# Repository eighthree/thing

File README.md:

# thing
Charlieplex matrix LED display with accelerometer

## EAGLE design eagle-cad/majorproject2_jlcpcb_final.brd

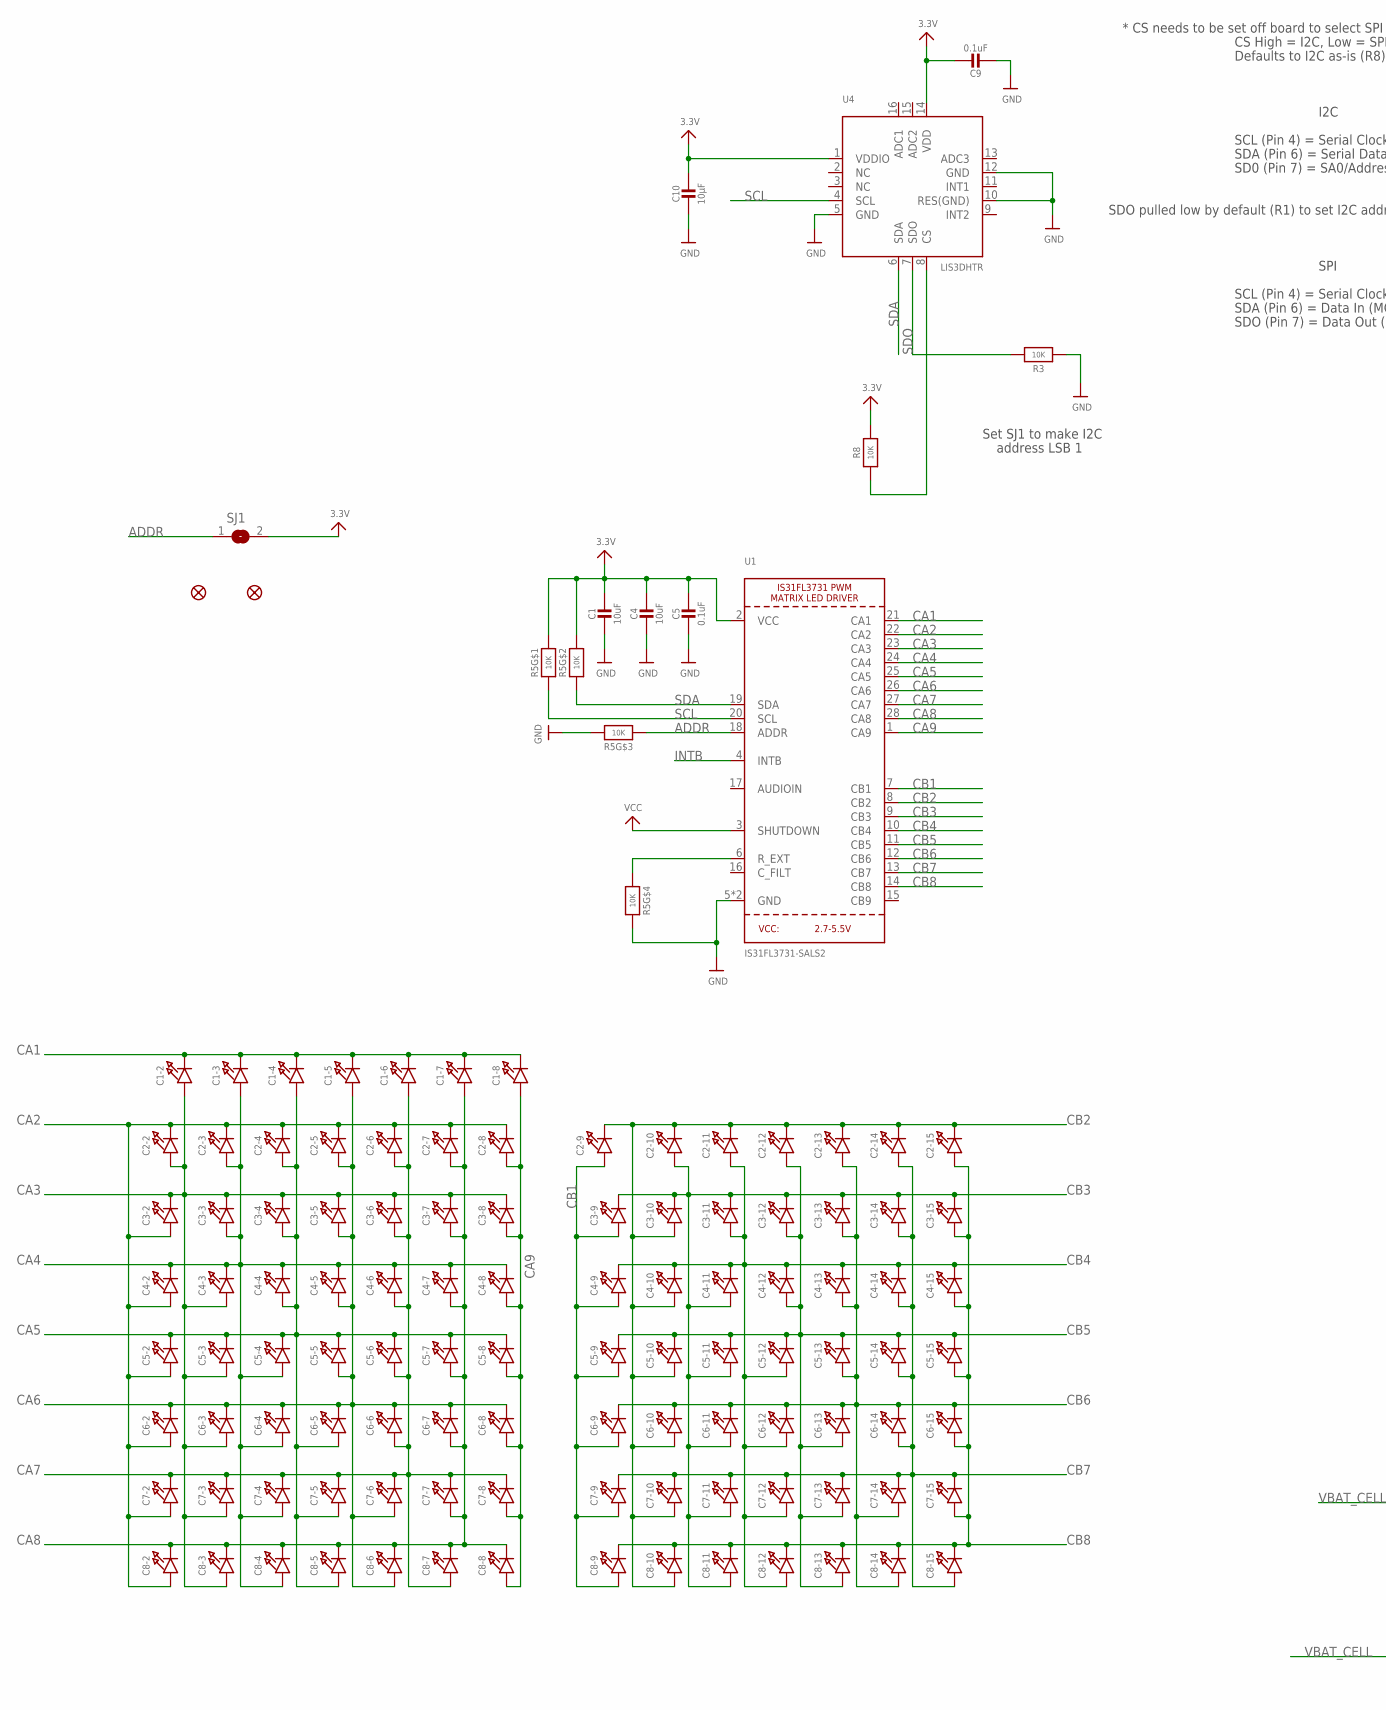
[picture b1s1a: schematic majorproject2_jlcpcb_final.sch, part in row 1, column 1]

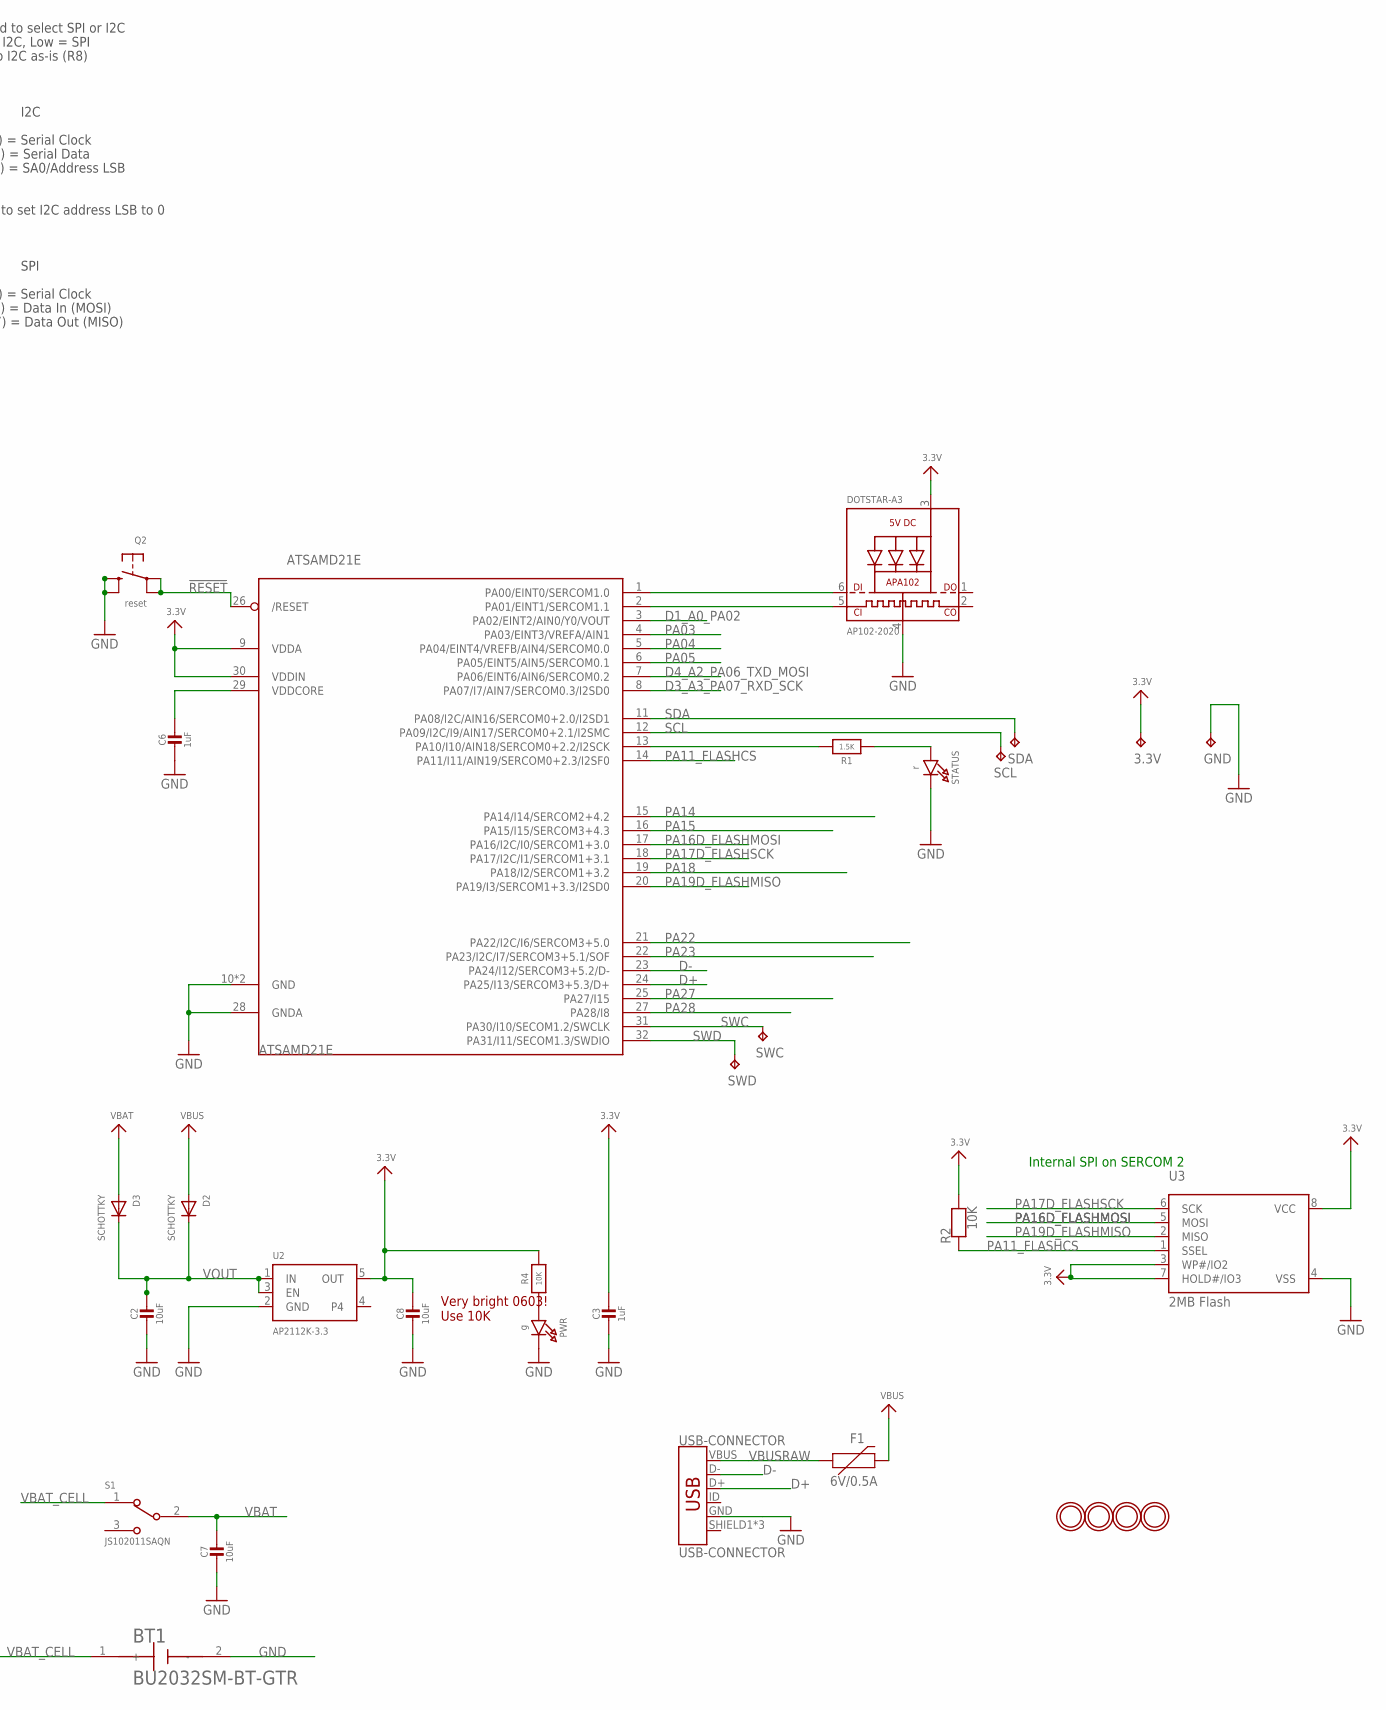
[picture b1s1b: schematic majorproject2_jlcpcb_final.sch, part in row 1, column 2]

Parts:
3.3V: TPB1,27; B1,27
ATSAMD21E: ATSAMD21E; QFN32_5MM
BT1: BU2032SM-BT-GTR; BAT_BU2032SM-BT-GTR
C1, C2, C4, C7, C8: 10uF; 0805-NO
C1-2, C1-3, C1-4, C1-5, C1-6, C1-7, C1-8, C2-2, C2-3, C2-4, C2-5, C2-6, C2-7, C2-8, C2-9, C2-10, C2-11, C2-12, C2-13, C2-14, C2-15, C3-2, C3-3, C3-4, C3-5, C3-6, C3-7, C3-8, C3-9, C3-10, C3-11, C3-12, C3-13, C3-14, C3-15, C4-2, C4-3, C4-4, C4-5, C4-6, C4-7, C4-8, C4-9, C4-10, C4-11, C4-12, C4-13, C4-14, C4-15, C5-2, C5-3, C5-4, C5-5, C5-6, C5-7, C5-8, C5-9, C5-10, C5-11, C5-12, C5-13, C5-14, C5-15, C6-2, C6-3, C6-4, C6-5, C6-6, C6-7, C6-8, C6-9, C6-10, C6-11, C6-12, C6-13, C6-14, C6-15, C7-2, C7-3, C7-4, C7-5, C7-6, C7-7, C7-8, C7-9, C7-10, C7-11, C7-12, C7-13, C7-14, C7-15, C8-2, C8-3, C8-4, C8-5, C8-6, C8-7, C8-8, C8-9, C8-10, C8-11, C8-12, C8-13, C8-14, C8-15: LED0603_NOOUTLINE; CHIPLED_0603_NOOUTLINE
C3, C6: 1uF; 0603-NO
C5: 0.1uF; 0805-NO
C9: 0.1uF; 0805_10MGAP
C10: 10µF; 0805-NO
D2, D3: SCHOTTKY; SOD-123FL
DOTSTAR-A3: AP102-2020; APA102_2020
F1: 6V/0.5A; 1206
FID1, FID2: FIDUCIAL""; FIDUCIAL_1MM
GND: TPB1,27; B1,27
PWR: g; CHIPLED_0603_NOOUTLINE
Q2: reset; BTN_KMR2_4.6X2.8
R1: 1.5K; 0603-NO
R2, R4: 10K; 0603-NO
R3, R8: 10K; 0805-NO
R5: 10K; RESPACK_4X0603
S1: JS102011SAQN; SW_JS102011SAQN
SCL: TPB1,27; B1,27
SDA: TPB1,27; B1,27
SJ1: SOLDERJUMPER; SOLDERJUMPER_ARROW_NOPASTE
STATUS: r; CHIPLED_0603_NOOUTLINE
SWC: TPB1,27; B1,27
SWD: TPB1,27; B1,27
U1: IS31FL3731-SALS2; QFN28_4MM_0.4MM
U2: AP2112K-3.3; SOT23-5
U3: 2MB Flash; SOIC8_208MIL
U4: LIS3DHTR; LGA16_3X3MM
U$20, U$21, U$22, U$23: MOUNTINGHOLE2.0; MOUNTINGHOLE_2.0_PLATED
USB-CONNECTOR: USB-CONNECTOR; USB-B-MICRO-SMD

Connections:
3.3V: 3.3V.TP, ATSAMD21E.9 (VDDA), ATSAMD21E.30 (VDDIN), C1.1, C3.1, C4.1, C5.1, C8.1, C9.1, C10.1, DOTSTAR-A3.3 (VDD), R2.2, R4.2, R5.7 (2), R5.8 (2), R8.2, SJ1.2, U1.2 (VCC), U2.5 (OUT), U3.3 (WP#/IO2), U3.7 (HOLD#/IO3), U3.8 (VCC), U4.1 (VDDIO), U4.14 (VDD)
!RESET: ATSAMD21E.26 (/RESET), Q2.A, Q2.A' (P1)
A3: ATSAMD21E.1 (PA00/EINT0/SERCOM1.0), DOTSTAR-A3.6 (DI)
ADDR: R5.3 (1), SJ1.1, U1.18 (ADDR)
CA1: C1-2.C, C1-3.C, C1-4.C, C1-5.C, C1-6.C, C1-7.C, C1-8.C, U1.21 (CA1)
CA2: C2-2.C, C2-3.C, C2-4.C, C2-5.C, C2-6.C, C2-7.C, C2-8.C, C3-2.A, C4-2.A, C5-2.A, C6-2.A, C7-2.A, C8-2.A, U1.22 (CA2)
CA3: C1-2.A, C2-2.A, C3-2.C, C3-3.C, C3-4.C, C3-5.C, C3-6.C, C3-7.C, C3-8.C, C4-3.A, C5-3.A, C6-3.A, C7-3.A, C8-3.A, U1.23 (CA3)
CA4: C1-3.A, C2-3.A, C3-3.A, C4-2.C, C4-3.C, C4-4.C, C4-5.C, C4-6.C, C4-7.C, C4-8.C, C5-4.A, C6-4.A, C7-4.A, C8-4.A, U1.24 (CA4)
CA5: C1-4.A, C2-4.A, C3-4.A, C4-4.A, C5-2.C, C5-3.C, C5-4.C, C5-5.C, C5-6.C, C5-7.C, C5-8.C, C6-5.A, C7-5.A, C8-5.A, U1.25 (CA5)
CA6: C1-5.A, C2-5.A, C3-5.A, C4-5.A, C5-5.A, C6-2.C, C6-3.C, C6-4.C, C6-5.C, C6-6.C, C6-7.C, C6-8.C, C7-6.A, C8-6.A, U1.26 (CA6)
CA7: C1-6.A, C2-6.A, C3-6.A, C4-6.A, C5-6.A, C6-6.A, C7-2.C, C7-3.C, C7-4.C, C7-5.C, C7-6.C, C7-7.C, C7-8.C, C8-7.A, U1.27 (CA7)
CA8: C1-7.A, C2-7.A, C3-7.A, C4-7.A, C5-7.A, C6-7.A, C7-7.A, C8-2.C, C8-3.C, C8-4.C, C8-5.C, C8-6.C, C8-7.C, C8-8.C, U1.28 (CA8)
CA9: C1-8.A, C2-8.A, C3-8.A, C4-8.A, C5-8.A, C6-8.A, C7-8.A, C8-8.A, U1.1 (CA9)
CB1: C2-9.A, C3-9.A, C4-9.A, C5-9.A, C6-9.A, C7-9.A, C8-9.A, U1.7 (CB1)
CB2: C2-9.C, C2-10.C, C2-11.C, C2-12.C, C2-13.C, C2-14.C, C2-15.C, C3-10.A, C4-10.A, C5-10.A, C6-10.A, C7-10.A, C8-10.A, U1.8 (CB2)
CB3: C2-10.A, C3-9.C, C3-10.C, C3-11.C, C3-12.C, C3-13.C, C3-14.C, C3-15.C, C4-11.A, C5-11.A, C6-11.A, C7-11.A, C8-11.A, U1.9 (CB3)
CB4: C2-11.A, C3-11.A, C4-9.C, C4-10.C, C4-11.C, C4-12.C, C4-13.C, C4-14.C, C4-15.C, C5-12.A, C6-12.A, C7-12.A, C8-12.A, U1.10 (CB4)
CB5: C2-12.A, C3-12.A, C4-12.A, C5-9.C, C5-10.C, C5-11.C, C5-12.C, C5-13.C, C5-14.C, C5-15.C, C6-13.A, C7-13.A, C8-13.A, U1.11 (CB5)
CB6: C2-13.A, C3-13.A, C4-13.A, C5-13.A, C6-9.C, C6-10.C, C6-11.C, C6-12.C, C6-13.C, C6-14.C, C6-15.C, C7-14.A, C8-14.A, U1.12 (CB6)
CB7: C2-14.A, C3-14.A, C4-14.A, C5-14.A, C6-14.A, C7-9.C, C7-10.C, C7-11.C, C7-12.C, C7-13.C, C7-14.C, C7-15.C, C8-15.A, U1.13 (CB7)
CB8: C2-15.A, C3-15.A, C4-15.A, C5-15.A, C6-15.A, C7-15.A, C8-9.C, C8-10.C, C8-11.C, C8-12.C, C8-13.C, C8-14.C, C8-15.C, U1.14 (CB8)
D1_A0_PA02: ATSAMD21E.3 (PA02/EINT2/AIN0/Y0/VOUT)
D3_A3_PA07_RXD_SCK: ATSAMD21E.8 (PA07/I7/AIN7/SERCOM0.3/I2SD0)
D4_A2_PA06_TXD_MOSI: ATSAMD21E.7 (PA06/EINT6/AIN6/SERCOM0.2)
D+: ATSAMD21E.24 (PA25/I13/SERCOM3+5.3/D+), USB-CONNECTOR.D+
D-: ATSAMD21E.23 (PA24/I12/SERCOM3+5.2/D-), USB-CONNECTOR.D-
GND: ATSAMD21E.10 (GND), ATSAMD21E.28 (GNDA), ATSAMD21E.33 (GND), BT1.2 (-), C1.2, C2.2, C3.2, C4.2, C5.2, C6.2, C7.2, C8.2, C9.2, C10.2, DOTSTAR-A3.4 (GND), GND.TP, PWR.C, Q2.B (S), Q2.B' (S1), R3.1, R5.5 (2), R5.6 (2), STATUS.C, U1.5 (GND), U1.THERMAL (GND), U2.2 (GND), U3.4 (VSS), U4.5 (GND), U4.10 (RES(GND)), U4.12 (GND), USB-CONNECTOR.GND
INTB: U1.4 (INTB)
unnamed: R1.1, STATUS.A
unnamed: ATSAMD21E.13 (PA10/I10/AIN18/SERCOM0+2.2/I2SCK), R1.2
unnamed: R8.1, U4.8 (CS)
unnamed: PWR.A, R4.1
unnamed: ATSAMD21E.2 (PA01/EINT1/SERCOM1.1), DOTSTAR-A3.5 (CKI)
PA03: ATSAMD21E.4 (PA03/EINT3/VREFA/AIN1)
PA04: ATSAMD21E.5 (PA04/EINT4/VREFB/AIN4/SERCOM0.0)
PA05: ATSAMD21E.6 (PA05/EINT5/AIN5/SERCOM0.1)
PA11_FLASHCS: ATSAMD21E.14 (PA11/I11/AIN19/SERCOM0+2.3/I2SF0), R2.1, U3.1 (SSEL)
PA14: ATSAMD21E.15 (PA14/I14/SERCOM2+4.2)
PA15: ATSAMD21E.16 (PA15/I15/SERCOM3+4.3)
PA16D_FLASHMOSI: ATSAMD21E.17 (PA16/I2C/I0/SERCOM1+3.0), U3.5 (MOSI)
PA17D_FLASHSCK: ATSAMD21E.18 (PA17/I2C/I1/SERCOM1+3.1), U3.6 (SCK)
PA18: ATSAMD21E.19 (PA18/I2/SERCOM1+3.2)
PA19D_FLASHMISO: ATSAMD21E.20 (PA19/I3/SERCOM1+3.3/I2SD0), U3.2 (MISO)
PA22: ATSAMD21E.21 (PA22/I2C/I6/SERCOM3+5.0)
PA23: ATSAMD21E.22 (PA23/I2C/I7/SERCOM3+5.1/SOF)
PA27: ATSAMD21E.25 (PA27/I15)
PA28: ATSAMD21E.27 (PA28/I8)
R_EXT: R5.4 (1), U1.6 (R_EXT)
SCL: ATSAMD21E.12 (PA09/I2C/I9/AIN17/SERCOM0+2.1/I2SMC), R5.1, SCL.TP, U1.20 (SCL), U4.4 (SCL)
SDA: ATSAMD21E.11 (PA08/I2C/AIN16/SERCOM0+2.0/I2SD1), R5.2 (1), SDA.TP, U1.19 (SDA), U4.6 (SDA)
SDO: R3.2, U4.7 (SDO)
SWC: ATSAMD21E.31 (PA30/I10/SECOM1.2/SWCLK), SWC.TP
SWD: ATSAMD21E.32 (PA31/I11/SECOM1.3/SWDIO), SWD.TP
VBAT: C7.1, D3.A, S1.2
VBAT_CELL: BT1.1 (+), S1.1
VBUS: D2.A, F1.2
VBUSRAW: F1.1, USB-CONNECTOR.VBUS
VCC: U1.3 (SHUTDOWN)
VDDCORE1: ATSAMD21E.29 (VDDCORE), C6.1
VOUT: C2.1, D2.C, D3.C, U2.1 (IN), U2.3 (EN)

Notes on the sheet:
Very bright 0603! Use 10K
Internal SPI on SERCOM 2
I2C
SCL (Pin 4) = Serial Clock
SDA (Pin 6) = Serial Data
SD0 (Pin 7) = SA0/Address LSB
* CS needs to be set off board to select SPI or I2C
CS High = I2C, Low = SPI
Defaults to I2C as-is (R8)
SDO pulled low by default (R1) to set I2C address LSB to 0
SPI
SDA (Pin 6) = Data In (MOSI)
SDO (Pin 7) = Data Out (MISO)
Set SJ1 to make I2C
address LSB 1

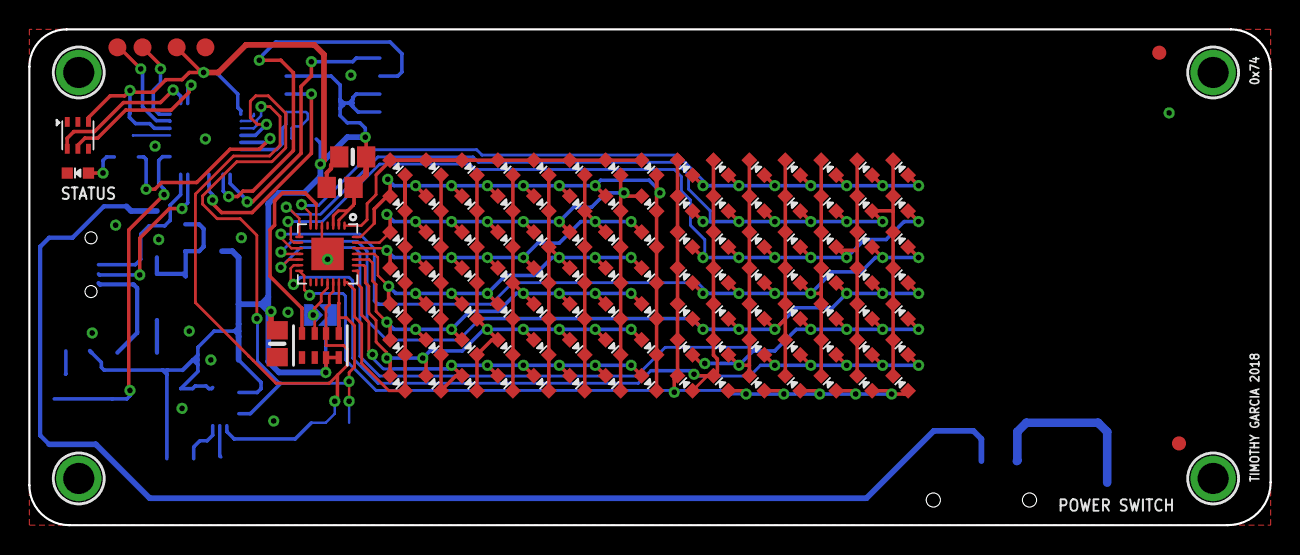
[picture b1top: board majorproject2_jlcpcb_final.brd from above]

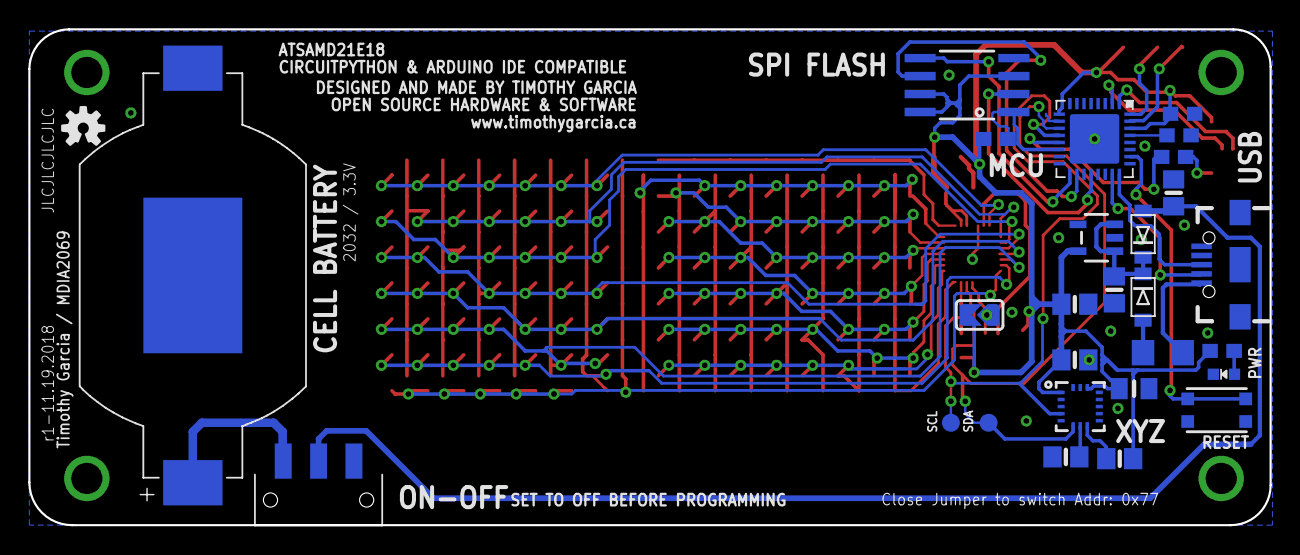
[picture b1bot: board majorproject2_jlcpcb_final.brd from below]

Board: 2 copper layers, 87.8 x 35.1 mm, 150 parts (28 on the bottom side), 45 nets.

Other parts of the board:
U$30: OSHW-LOGO-S

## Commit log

2018-12-12 Device firmware
2018-12-12 Add files via upload
    Laser cut enclosure source file
2018-12-13 Add files via upload
    Alpha 4.5

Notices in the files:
parts and their libraries:
microbuilder: This work is placed in the public domain, and may be freely used for commercial and non-commercial work with the following conditions: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
SparkFun-Connectors: Licensing: Creative Commons ShareAlike 4.0 International - https://creativecommons.org/licenses/by-sa/4.0
